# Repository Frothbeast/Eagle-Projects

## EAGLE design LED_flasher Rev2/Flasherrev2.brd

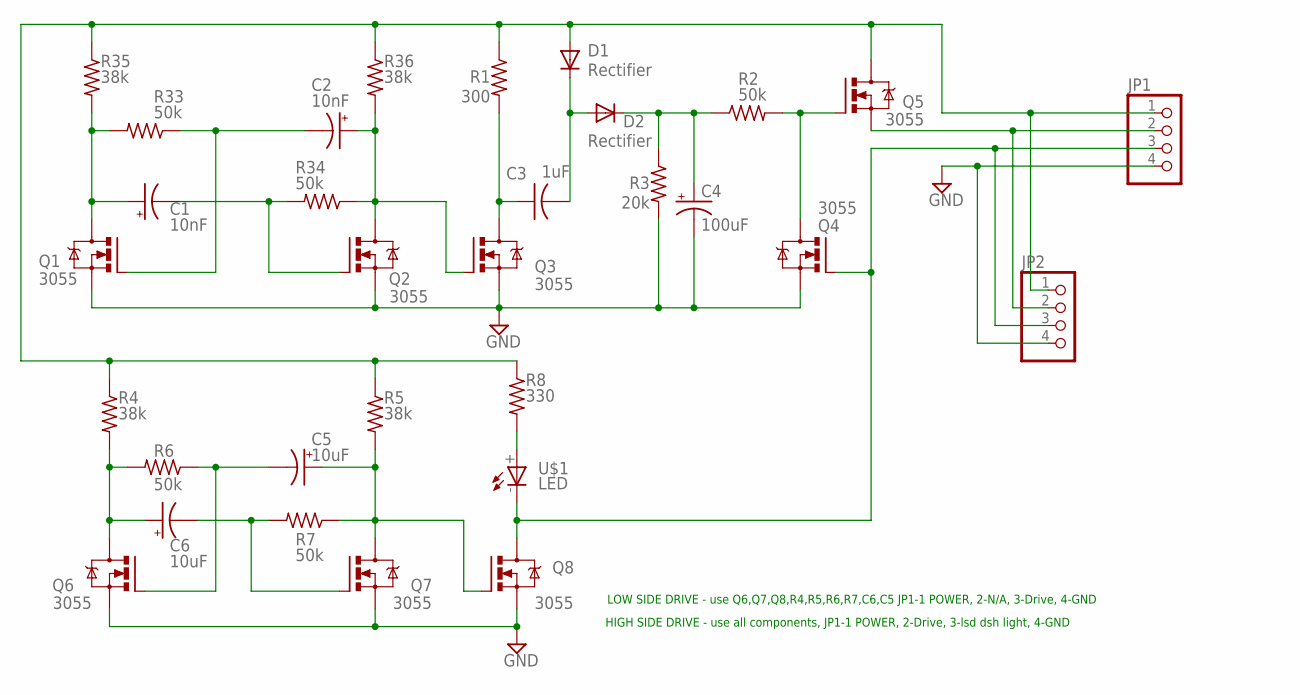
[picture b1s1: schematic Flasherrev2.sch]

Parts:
C1, C2: 10nF; CT3528
C3: 1uF; C1206
C4: 100uF; PANASONIC_F
C5, C6: 10uF; CT3528
D1, D2: Rectifier; DO-214AC
JP1, JP2: PINHD-1X4; 1X04
Q1, Q2, Q3, Q4, Q6, Q7: 3055; SOT223R_INFINEON
Q5, Q8: 3055; TO220BV
R1: 300; R1206
R2, R6, R7, R33, R34: 50k; R1206
R3: 20k; R1206
R4, R5, R35, R36: 38k; R1206
R8: 330; R1206
U$1: LED; 1206

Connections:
GND: C4.-, JP1.4, JP2.4, Q1.3 (S), Q2.3 (S), Q3.3 (S), Q4.3 (S), Q6.3 (S), Q7.3 (S), Q8.S, R3.2
unnamed: C4.+, D2.C, R2.1, R3.1
unnamed: C3.2, D1.C, D2.A
unnamed: JP1.3, JP2.3, Q4.1 (G), Q8.D, U$1.-
unnamed: JP1.2, JP2.2, Q5.S
unnamed: R8.2, U$1.+
unnamed: Q4.2 (D), Q5.G, R2.2
unnamed: C6.+, Q6.2 (D), R4.2, R6.2
unnamed: C5.-, Q6.1 (G), R6.1
unnamed: C1.+, Q1.2 (D), R33.2, R35.2
unnamed: C2.+, Q2.2 (D), Q3.1 (G), R34.1, R36.2
unnamed: C6.-, Q7.1 (G), R7.2
unnamed: C2.-, Q1.1 (G), R33.1
unnamed: C1.-, Q2.1 (G), R34.2
unnamed: C5.+, Q7.2 (D), Q8.G, R5.2, R7.1
unnamed: D1.A, JP1.1, JP2.1, Q5.D, R1.1, R4.1, R5.1, R8.1, R35.1, R36.1
unnamed: C3.1, Q3.2 (D), R1.2

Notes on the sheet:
LOW SIDE DRIVE - use Q6,Q7,Q8,R4,R5,R6,R7,C6,C5 JP1-1 POWER, 2-N/A, 3-Drive, 4-GND
HIGH SIDE DRIVE - use all components, JP1-1 POWER, 2-Drive, 3-lsd dsh light, 4-GND

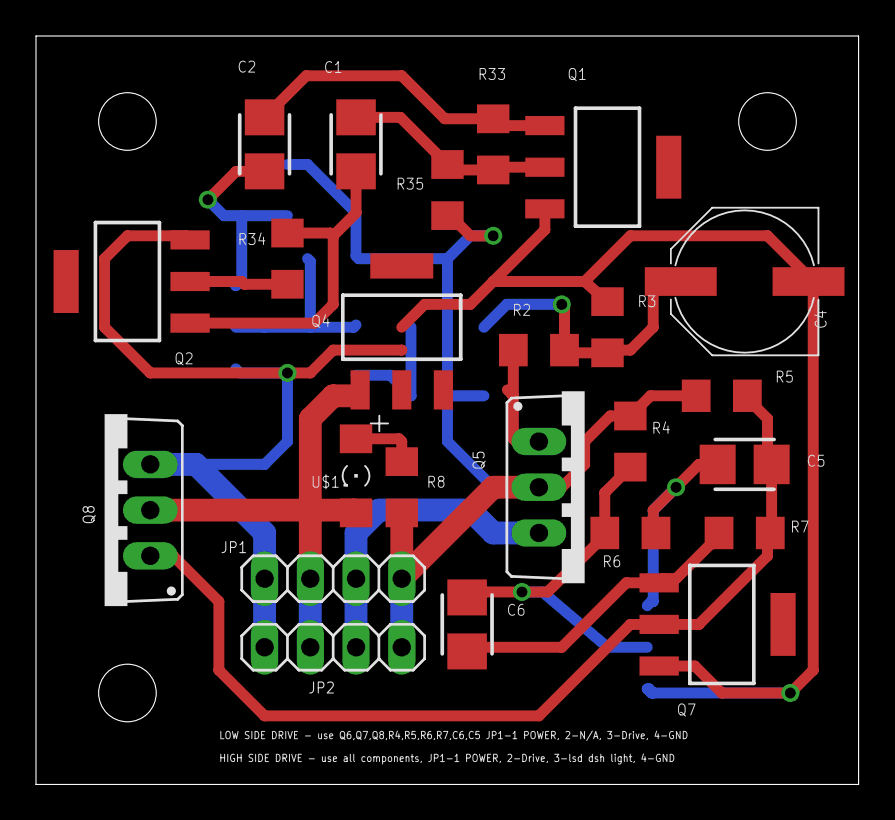
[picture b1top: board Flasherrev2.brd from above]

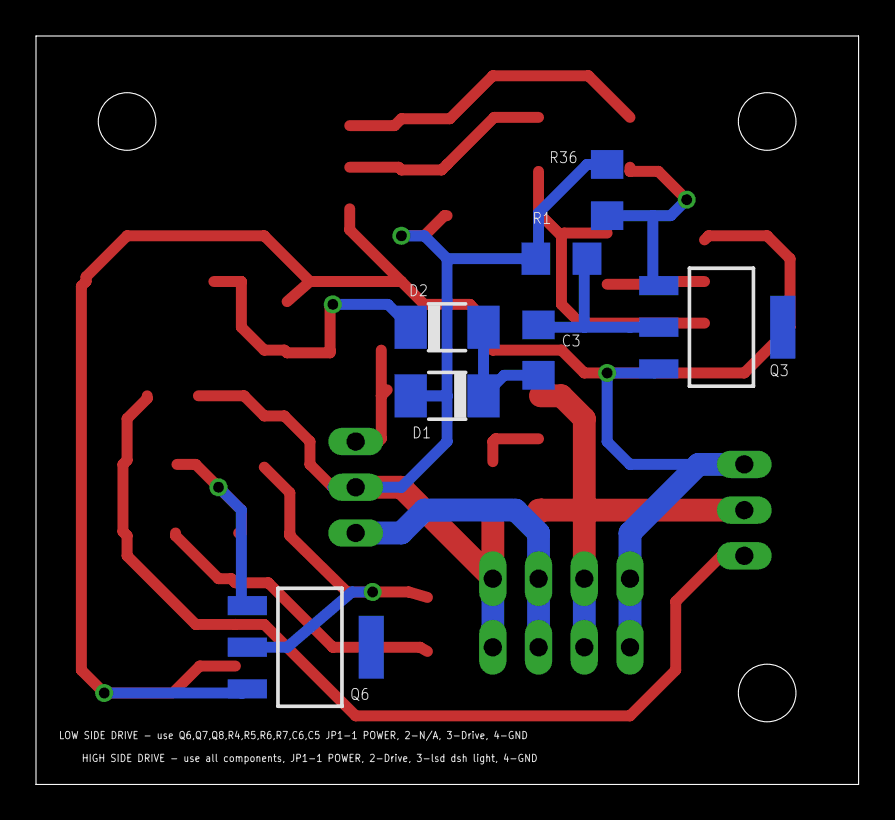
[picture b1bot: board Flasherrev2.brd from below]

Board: 2 copper layers, 45.7 x 41.6 mm, 34 parts (7 on the bottom side), 17 nets.

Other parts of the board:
U$2, U$3, U$4: SCREW

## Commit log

2023-08-22 Adding my eagle code to git
2025-12-16 found latest revisions on a different computer so now uploading
2025-12-16 added Small parts drawers.xls
2025-12-16 added PDF
2025-12-17 added first list of pins
2025-12-18 added image of schematic to cross off all the components to make sure they are all in the list
2025-12-19 updated the csv file and diagram of parts added to the csv file
    When complete, the CSV file will have teh complete BOM of a generalIO board which can be populated minimally for what is needed
2026-01-14 removed x column and added some more rows
2026-01-14 added pdf that hopefully prints larger
2026-01-19 added to small parts drawers
2026-01-19 added mini rev 3 for sumpWifi schematics
2026-01-20 more added
2026-01-22 added proto board
2026-04-06 updated some drawers
